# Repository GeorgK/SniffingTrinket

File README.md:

SniffingTrinket
===============

A room climate monitor using the Adafruit Trinket Pro

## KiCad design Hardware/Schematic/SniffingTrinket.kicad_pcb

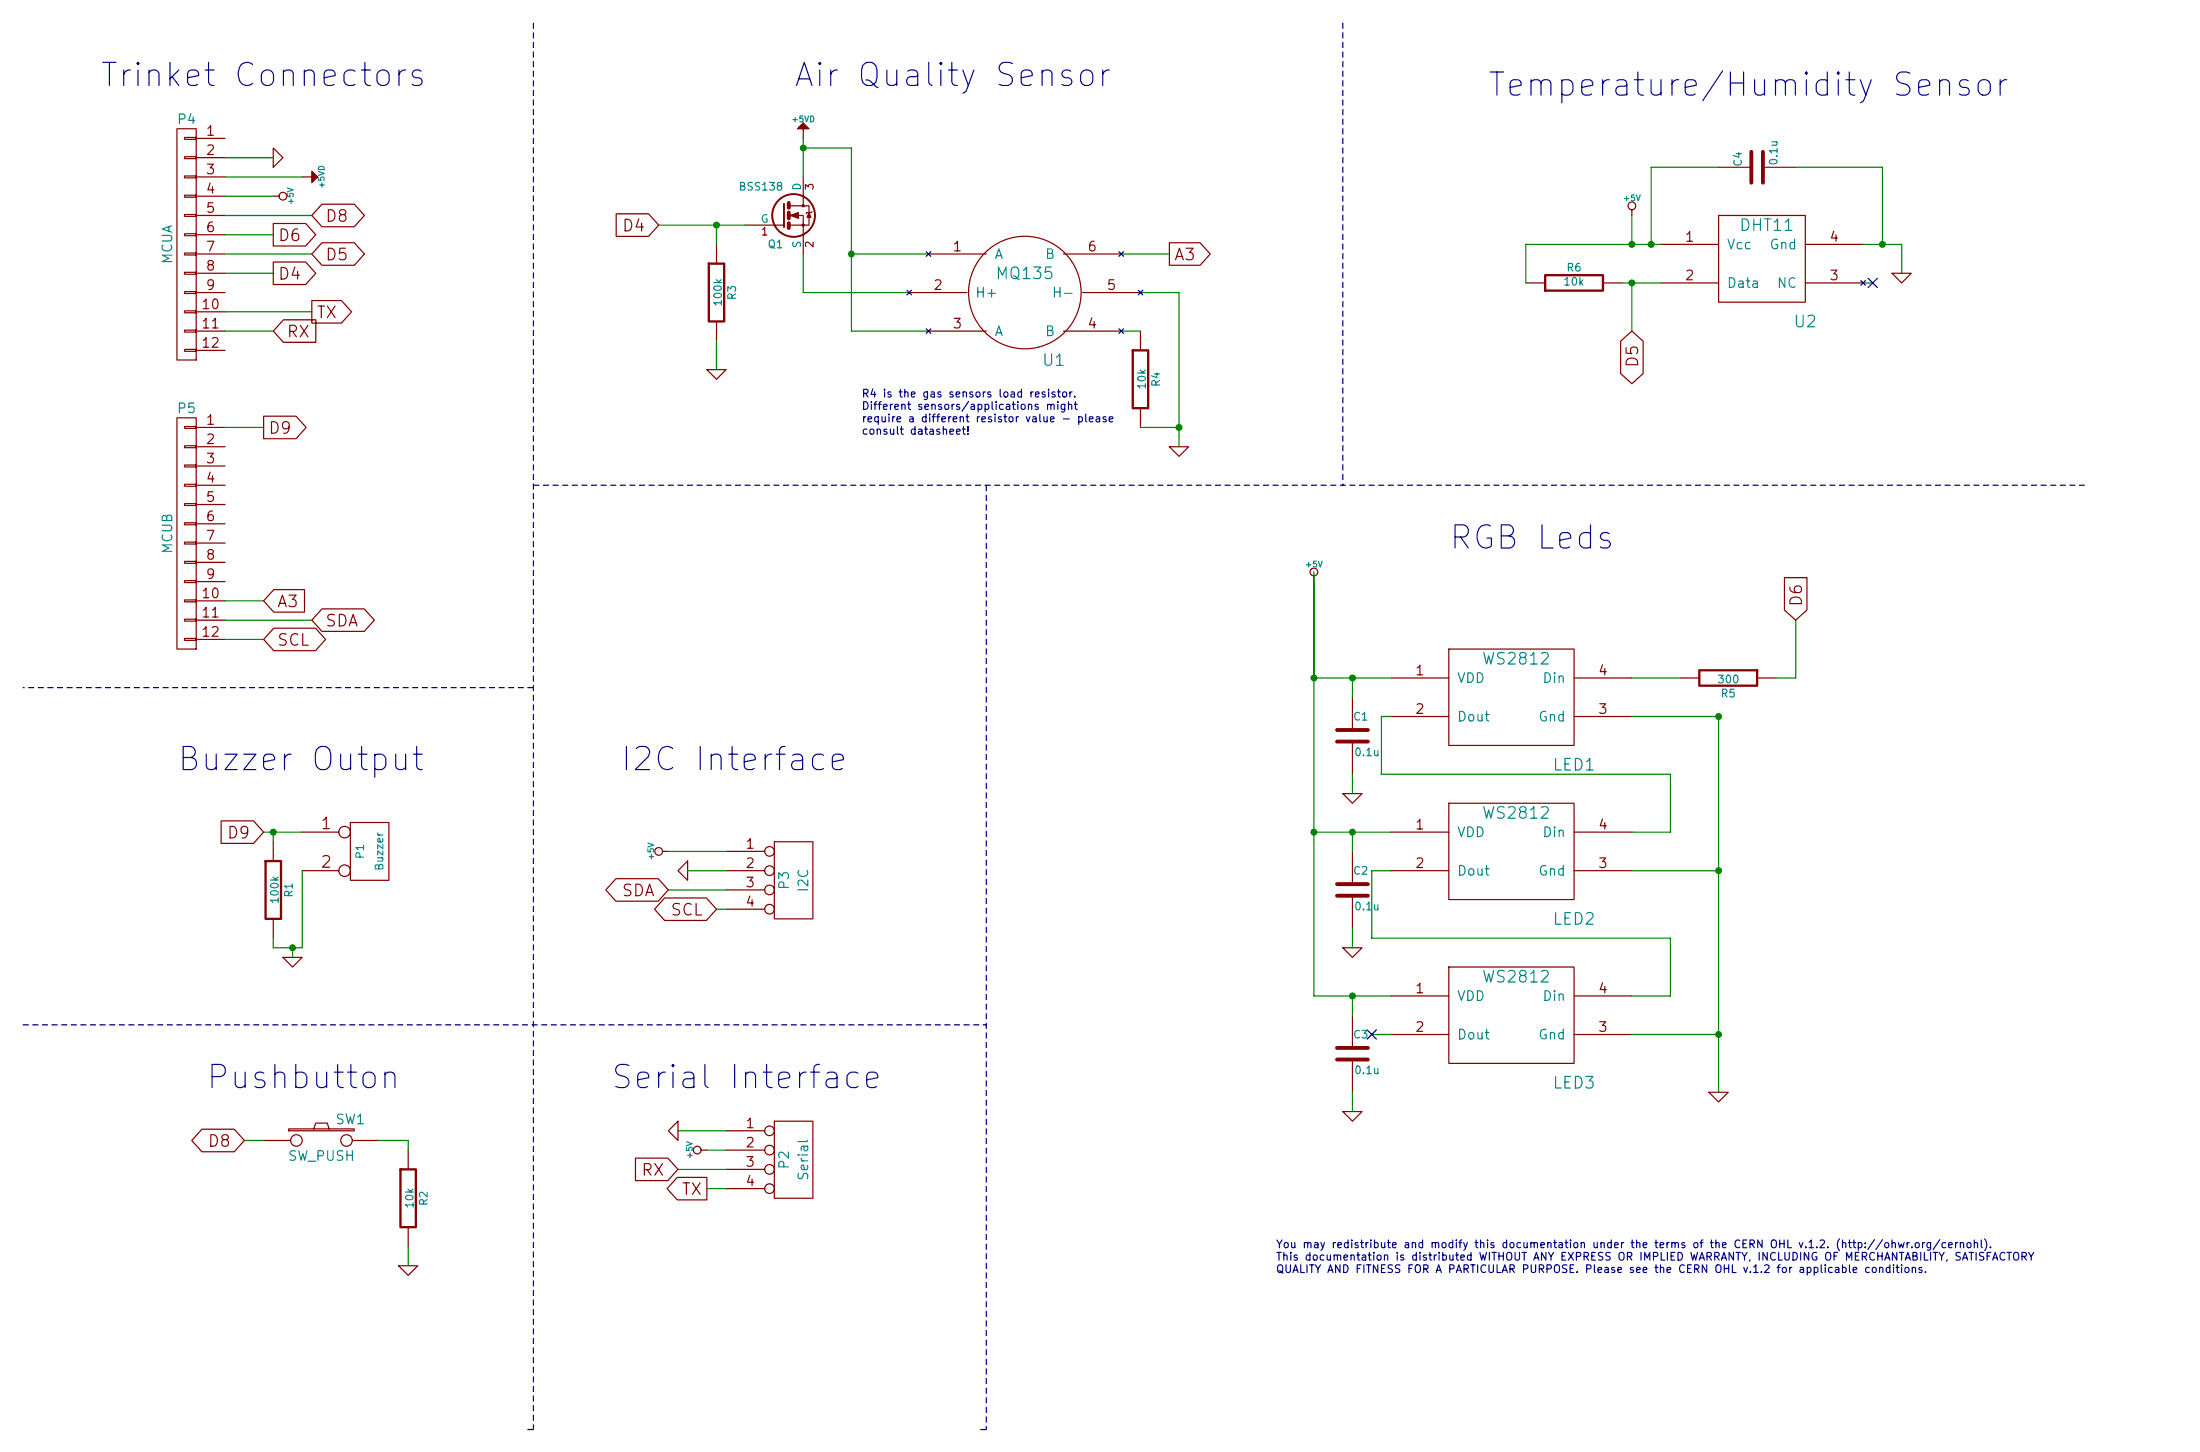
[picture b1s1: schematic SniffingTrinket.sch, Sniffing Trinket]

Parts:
C1, C2, C3, C4: 0.1u; SMD-0805
LED1, LED2, LED3: WS2812; WS2812B
P1: Buzzer; Pin_Header_Straight_1x02
P2: Serial; Pin_Header_Straight_1x04
P3: I2C; Pin_Header_Straight_1x04
P4: MCUA; Pin_Header_Straight_1x12
P5: MCUB; Pin_Header_Straight_1x12
Q1: BSS138; SOT-23
R1, R3: 100k; SMD-0805
R2, R4, R6: 10k; SMD-0805
R5: 300; SMD-0805
SW1: SW_PUSH; PUSH_BUTT_SHAPE1
U1: MQ135
U2: DHT11; Pin_Header_Straight_1x04

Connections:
+5V: C1.1, C2.1, C3.1, C4.1, LED1.1 (VDD), LED2.1 (VDD), LED3.1 (VDD), P2.2, P3.1, P4.4, R6.1, U2.1 (Vcc)
+5VD: P4.3, Q1.3 (D), U1.1 (A), U1.3 (A)
A3: P5.10, U1.6 (B)
D4: P4.8, Q1.1 (G), R3.1
D5: P4.7, R6.2, U2.2 (Data)
D6: P4.6, R5.1
D8: P4.5, SW1.1
D9: P1.1, P5.1, R1.1
GND: C1.2, C2.2, C3.2, C4.2, LED1.3 (Gnd), LED2.3 (Gnd), LED3.3 (Gnd), P1.2 (PM), P2.1, P3.2, P4.2, R1.2, R2.2, R3.2, R4.2, U1.5 (H-), U2.4 (Gnd)
unnamed: LED1.2 (Dout), LED2.4 (Din)
unnamed: LED1.4 (Din), R5.2
unnamed: LED2.2 (Dout), LED3.4 (Din)
unnamed: Q1.2 (S), U1.2 (H+)
unnamed: R2.1, SW1.2
unnamed: R4.1, U1.4 (B)
RX: P2.3, P4.11
SCL: P3.4, P5.12
SDA: P3.3, P5.11
TX: P2.4, P4.10

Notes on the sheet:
Air Quality Sensor
Temperature/Humidity Sensor
Serial Interface
Pushbutton
Buzzer Output
I2C Interface
Trinket Connectors
RGB Leds
R4 is the gas sensors load resistor. Different sensors/applications might require a different resistor value - please consult datasheet!
You may redistribute and modify this documentation under the terms of the CERN OHL v.1.2. (http://ohwr.org/cernohl). This documentation is distributed WITHOUT ANY EXPRESS OR IMPLIED WARRANTY, INCLUDING OF MERCHANTABILITY, SATISFACTORY QUALITY AND FITNESS FOR A PARTICULAR PURPOSE. Please see the CER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

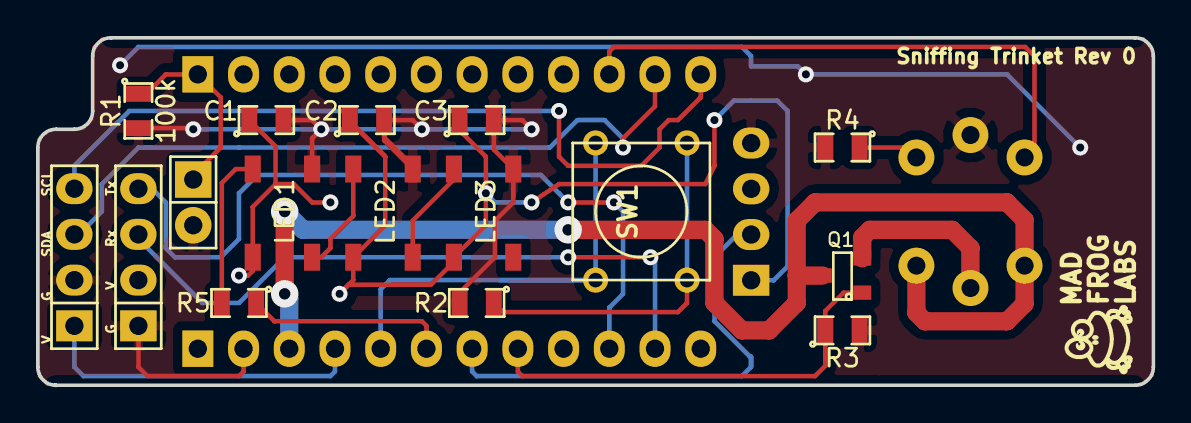
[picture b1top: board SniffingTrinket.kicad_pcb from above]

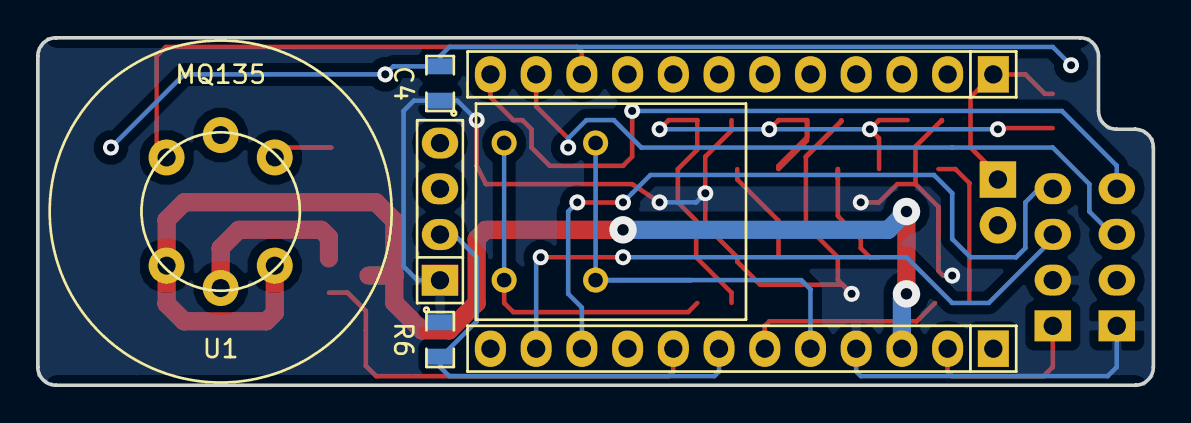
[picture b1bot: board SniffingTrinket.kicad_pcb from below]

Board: 2 copper layers, 62.0 x 19.3 mm, 22 parts (6 on the bottom side), 19 nets.

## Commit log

2014-12-29 Adding Hardware files
2014-12-31 Add the arduino sketches

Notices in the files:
Hardware/Schematic/SniffingTrinket.sch:
This documentation is licensed under the CERN OHL v. 1.2.
Copyright Georg Krocker 2014
